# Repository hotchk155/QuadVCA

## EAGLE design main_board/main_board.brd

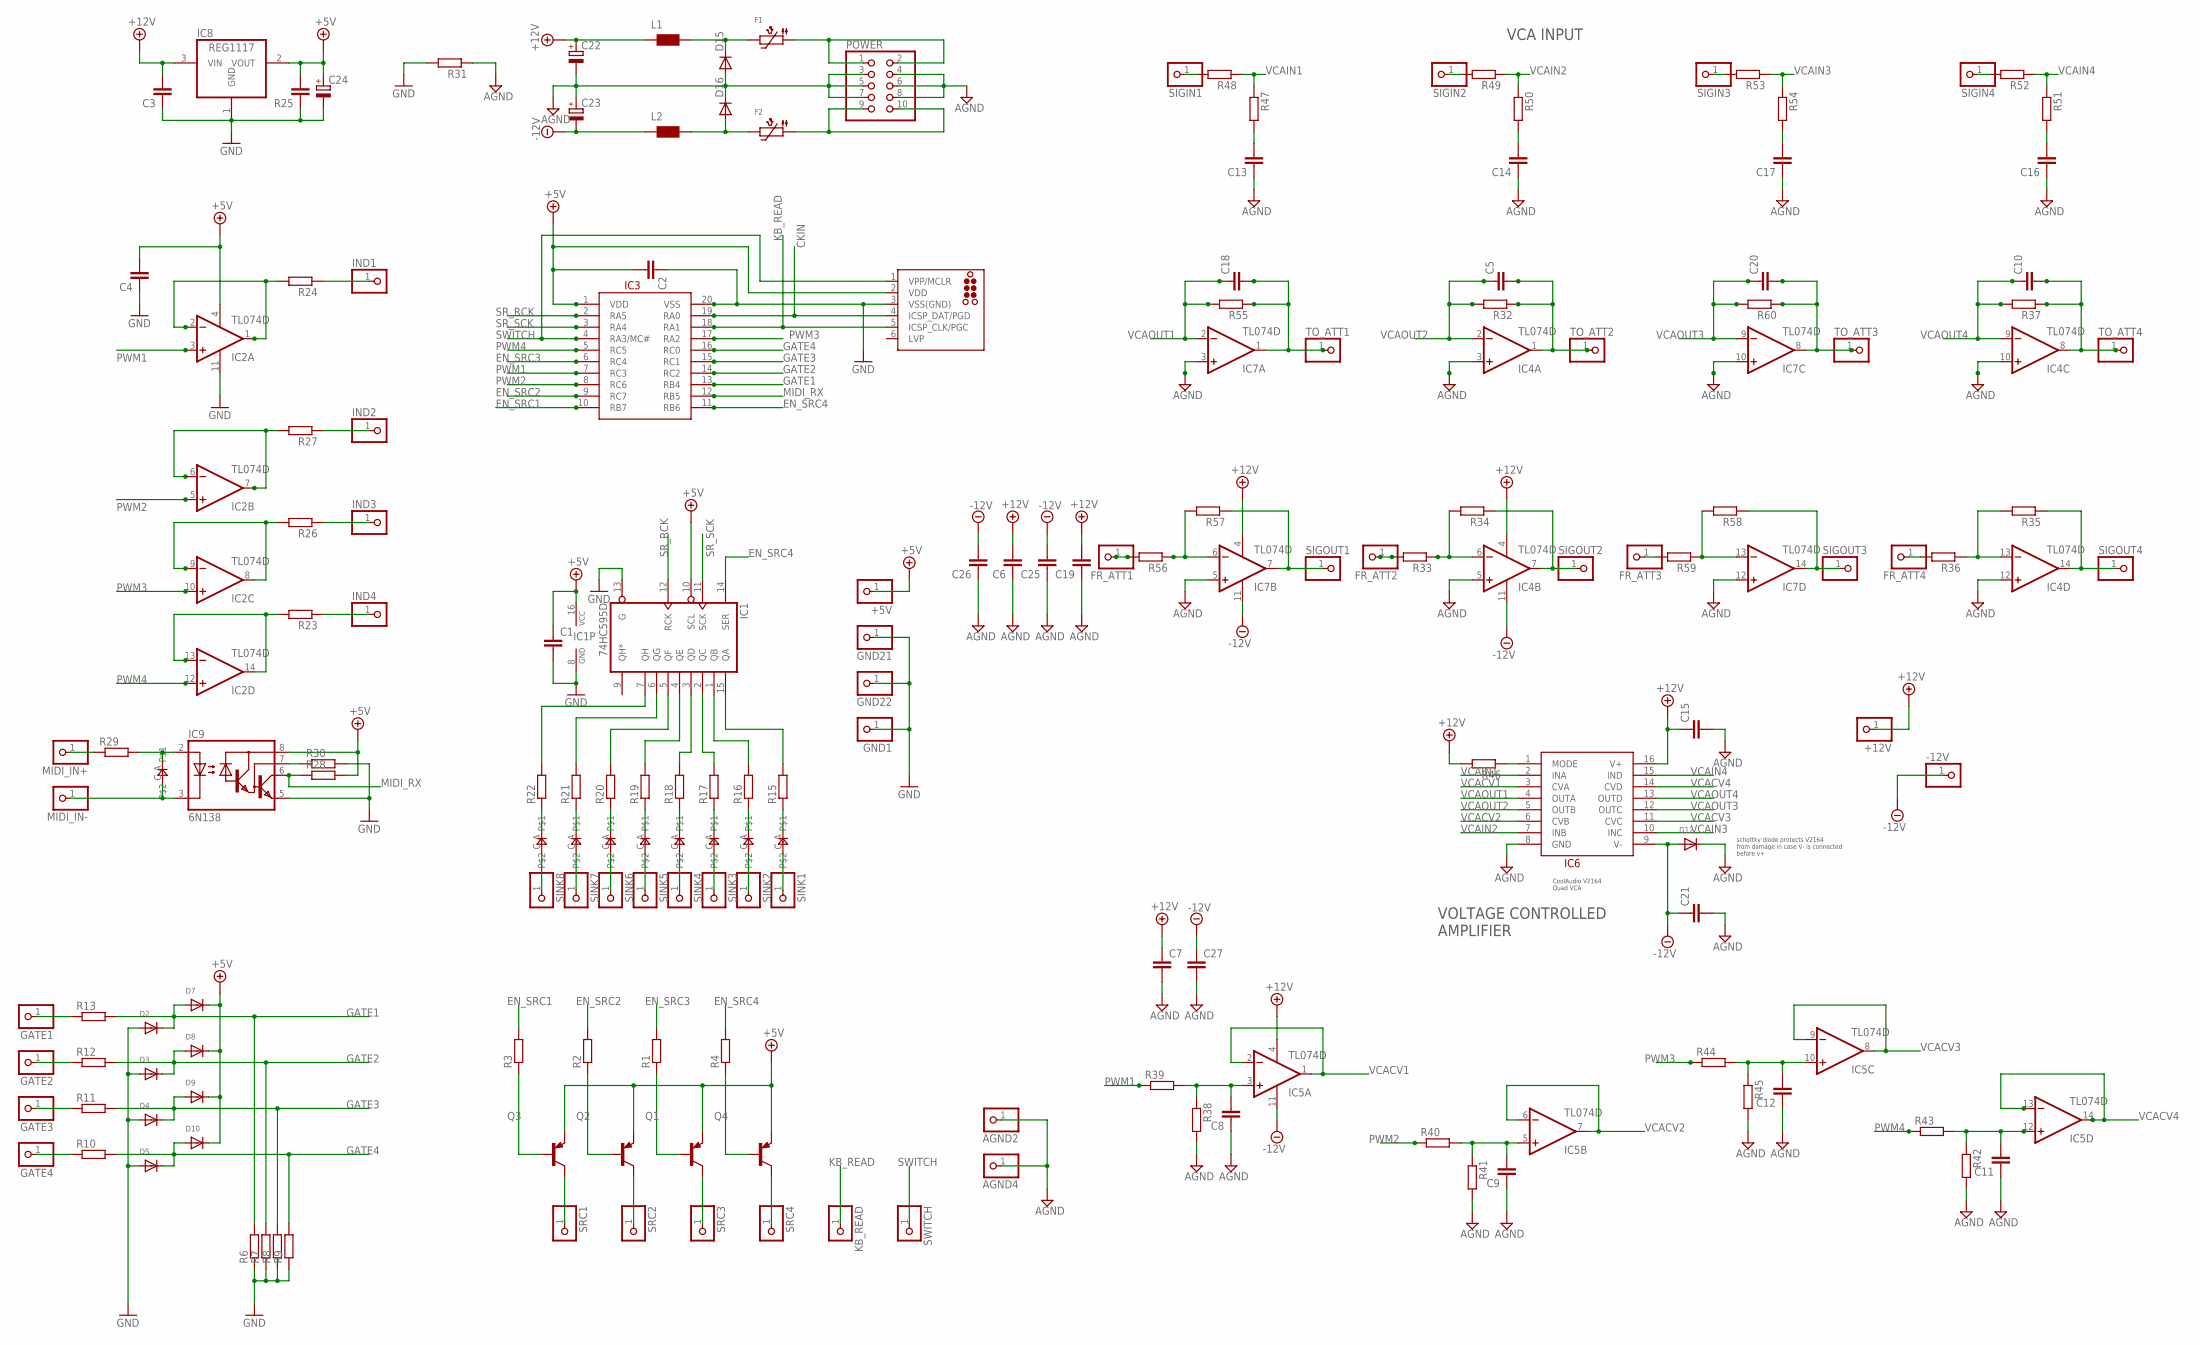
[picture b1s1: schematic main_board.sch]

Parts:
+5V, +12V: PINHD-1X1; 1X01
-12V: PINHD-1X1; 1X01
AGND2, AGND4: PINHD-1X1; 1X01
C1, C2, C3, C4, C5, C6, C7, C8, C9, C10, C11, C12, C13, C14, C15, C16, C17, C18, C19, C20, C21, C25, C26, C27: C-EUC0805; C0805
C22, C23: CPOL-EUE2.5-7; E2,5-7
C24: CPOL-EUE2.5-5; E2,5-5
D2, D3, D4, D5, D7, D8, D9, D10, D12: DIODESOD-123; SOD-123
D11, D13, D14, D17, D18, D19, D20, D21, D22: 0805DIODE
D15, D16: MBR0520LT; SOD123
F1, F2: PTC1210
FR_ATT1, FR_ATT2, FR_ATT3, FR_ATT4: PINHD-1X1; 1X01
GATE1, GATE2, GATE3, GATE4: PINHD-1X1; 1X01
GND1, GND21, GND22: PINHD-1X1; 1X01
IC1: 74HC595D; SO16
IC2, IC4, IC5, IC7: TL074D; SO14
IC3: PIC16F1829SOIC; SO20W
IC6: V2164; SO16
IC8: REG1117; SOT223
IC9: 6N138; DIL08
ICSP: TC2030-MCP-NL
IND1, IND2, IND3, IND4: PINHD-1X1; 1X01
KB_READ: PINHD-1X1; 1X01
L1, L2: WE-CBF_0805; 0805
MIDI_IN+: PINHD-1X1; 1X01
MIDI_IN-: PINHD-1X1; 1X01
POWER: PINHD-2X5; 2X05
Q1, Q2, Q3, Q4: MMBT3906LT1-PNP-SOT23-BEC; SOT23-BEC
R1, R2, R3, R4, R6, R7, R8, R9, R10, R11, R12, R13, R15, R16, R17, R18, R19, R20, R21, R22, R23, R24, R26, R27, R28, R29, R30, R31, R32, R33, R34, R35, R36, R37, R38, R39, R40, R41, R42, R43, R44, R45, R46, R47, R48, R49, R50, R51, R52, R53, R54, R55, R56, R57, R58, R59, R60: R-EU_R0805; R0805
R25: C-EUC0805; C0805
SIGIN1, SIGIN2, SIGIN3, SIGIN4: PINHD-1X1; 1X01
SIGOUT1, SIGOUT2, SIGOUT3, SIGOUT4: PINHD-1X1; 1X01
SINK1, SINK2, SINK3, SINK4, SINK5, SINK6, SINK7, SINK8: PINHD-1X1; 1X01
SRC1, SRC2, SRC3, SRC4: PINHD-1X1; 1X01
SWITCH: PINHD-1X1; 1X01
TO_ATT1, TO_ATT2, TO_ATT3, TO_ATT4: PINHD-1X1; 1X01

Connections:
+5V: +5V.1, C1.1, C2.2, C4.2, C24.+, D7.C, D8.C, D9.C, D10.C, IC1.10 (SCL), IC1.16 (VCC), IC2.4 (V+), IC3.1 (VDD), IC8.2 (VOUT), IC9.8 (VCC), ICSP.2 (VDD), Q1.E, Q2.E, Q3.E, Q4.E, R25.2, R28.2
+12V: +12V.1, C3.2, C6.2, C7.1, C15.1, C19.2, C22.+, IC4.4 (V+), IC5.4 (V+), IC6.16 (V+), IC7.4 (V+), IC8.3 (VIN), L1.1, R46.2
-12V: -12V.1, C21.1, C23.-, C25.2, C26.2, C27.1, D12.A, IC4.11 (V-), IC5.11 (V-), IC6.9 (V-), IC7.11 (V-), L2.1
AGND: AGND2.1, AGND4.1, C6.1, C7.2, C8.1, C9.1, C11.1, C12.1, C13.1, C14.1, C15.2, C16.1, C17.1, C19.1, C21.2, C22.-, C23.+, C25.1, C26.1, C27.2, D12.C, D15.A, D16.C, IC4.3 (+IN), IC4.5 (+IN), IC4.10 (+IN), IC4.12 (+IN), IC6.8 (GND), IC7.3 (+IN), IC7.5 (+IN), IC7.10 (+IN), IC7.12 (+IN), POWER.3, POWER.4, POWER.5, POWER.6, POWER.7, POWER.8, R31.1, R38.2, R41.2, R42.2, R45.2
CKIN: IC3.19 (RA0), ICSP.4 (ICSP_DAT/PGD)
EN_SRC1: IC3.10 (RB7), R3.2
EN_SRC2: IC3.9 (RC7), R2.2
EN_SRC3: IC3.6 (RC4), R1.2
EN_SRC4: IC1.14 (SER), IC3.11 (RB6), R4.2
FR_ATT1: FR_ATT1.1, R56.2
GATE1: D2.C, D7.A, IC3.13 (RB4), R6.2, R13.2
GATE2: D3.C, D8.A, IC3.14 (RC2), R7.2, R12.2
GATE3: D4.C, D9.A, IC3.15 (RC1), R8.2, R11.2
GATE4: D5.C, D10.A, IC3.16 (RC0), R9.2, R10.2
GND: C1.2, C2.1, C3.1, C4.1, C24.-, D2.A, D3.A, D4.A, D5.A, GND1.1, GND21.1, GND22.1, IC1.8 (GND), IC1.13 (G), IC2.11 (V-), IC3.20 (VSS), IC8.1 (GND), IC9.5 (GND), ICSP.3 (VSS(GND)), R6.1, R7.1, R8.1, R9.1, R25.1, R30.2, R31.2
KB_READ: IC3.18 (RA1), ICSP.5 (ICSP_CLK/PGC), KB_READ.1
MIDI_RX: IC3.12 (RB5), IC9.6 (VO), R28.1
unnamed: IC1.7 (QH), R22.2
unnamed: IC1.6 (QG), R21.2
unnamed: IC1.5 (QF), R20.2
unnamed: IC1.4 (QE), R19.2
unnamed: IC1.3 (QD), R18.2
unnamed: IC1.2 (QC), R17.2
unnamed: IC1.1 (QB), R16.2
unnamed: IC1.15 (QA), R15.2
unnamed: D13.A, R22.1
unnamed: D14.A, R21.1
unnamed: D17.A, R20.1
unnamed: D18.A, R19.1
unnamed: D19.A, R18.1
unnamed: D20.A, R17.1
unnamed: D21.A, R16.1
unnamed: D22.A, R15.1
unnamed: Q3.C, SRC1.1
unnamed: Q2.C, SRC2.1
unnamed: Q1.C, SRC3.1
unnamed: Q4.C, SRC4.1
unnamed: IC6.1 (MODE), R46.1
unnamed: Q3.B, R3.1
unnamed: Q2.B, R2.1
unnamed: Q1.B, R1.1
unnamed: Q4.B, R4.1
unnamed: D13.C, SINK8.1
unnamed: IC7.6 (-IN), R56.1, R57.2
unnamed: IC7.7 (OUT), R57.1, SIGOUT1.1
unnamed: D14.C, SINK7.1
unnamed: IC7.13 (-IN), R58.2, R59.1
unnamed: IC7.14 (OUT), R58.1, SIGOUT3.1
unnamed: D15.C, F1.P$2 (2), L1.2
unnamed: IC4.6 (-IN), R33.1, R34.2
unnamed: IC4.7 (OUT), R34.1, SIGOUT2.1
unnamed: D16.A, F2.P$2 (2), L2.2
unnamed: IC4.13 (-IN), R35.2, R36.1
unnamed: IC4.14 (OUT), R35.1, SIGOUT4.1
unnamed: C13.2, R47.2
unnamed: R48.2, SIGIN1.1
unnamed: C14.2, R50.2
unnamed: R49.2, SIGIN2.1
unnamed: C17.2, R54.2
unnamed: R53.2, SIGIN3.1
unnamed: C16.2, R51.2
unnamed: R52.2, SIGIN4.1
unnamed: IND1.1, R24.1
unnamed: IC2.1 (OUT), IC2.2 (-IN), R24.2
unnamed: C8.2, IC5.3 (+IN), R38.1, R39.2
unnamed: D17.C, SINK6.1
unnamed: IC2.6 (-IN), IC2.7 (OUT), R27.2
unnamed: IND2.1, R27.1
unnamed: C9.2, IC5.5 (+IN), R40.2, R41.1
unnamed: IC2.8 (OUT), IC2.9 (-IN), R26.2
unnamed: IND3.1, R26.1
unnamed: C12.2, IC5.10 (+IN), R44.2, R45.1
unnamed: IC2.13 (-IN), IC2.14 (OUT), R23.2
unnamed: IND4.1, R23.1
unnamed: C11.2, IC5.12 (+IN), R42.1, R43.2
unnamed: D18.C, SINK5.1
unnamed: FR_ATT2.1, R33.2
unnamed: GATE1.1, R13.1
unnamed: IC9.7 (VB), R30.1
unnamed: F2.P$1 (1), POWER.9, POWER.10
unnamed: D11.A, IC9.2 (A), R29.2
unnamed: D11.C, IC9.3 (C), MIDI_IN-.1
unnamed: MIDI_IN+.1, R29.1
unnamed: GATE2.1, R12.1
unnamed: GATE3.1, R11.1
unnamed: GATE4.1, R10.1
unnamed: FR_ATT3.1, R59.2
unnamed: FR_ATT4.1, R36.2
unnamed: D19.C, SINK4.1
unnamed: D20.C, SINK3.1
unnamed: F1.P$1 (1), POWER.1, POWER.2
unnamed: D21.C, SINK2.1
unnamed: D22.C, SINK1.1
PWM1: IC2.3 (+IN), IC3.7 (RC3), R39.1
PWM2: IC2.5 (+IN), IC3.8 (RC6), R40.1
PWM3: IC2.10 (+IN), IC3.17 (RA2), R44.1
PWM4: IC2.12 (+IN), IC3.5 (RC5), R43.1
SR_RCK: IC1.12 (RCK), IC3.2 (RA5)
SR_SCK: IC1.11 (SCK), IC3.3 (RA4)
SWITCH: IC3.4 (RA3/MC#), ICSP.1 (VPP/MCLR), SWITCH.1
TO_ATT1: C18.2, IC7.1 (OUT), R55.1, TO_ATT1.1
TO_ATT2: C5.2, IC4.1 (OUT), R32.1, TO_ATT2.1
TO_ATT3: C20.2, IC7.8 (OUT), R60.1, TO_ATT3.1
TO_ATT4: C10.2, IC4.8 (OUT), R37.1, TO_ATT4.1
VCACV1: IC5.1 (OUT), IC5.2 (-IN), IC6.3 (CVA)
VCACV2: IC5.6 (-IN), IC5.7 (OUT), IC6.6 (CVB)
VCACV3: IC5.8 (OUT), IC5.9 (-IN), IC6.11 (CVC)
VCACV4: IC5.13 (-IN), IC5.14 (OUT), IC6.14 (CVD)
VCAIN1: IC6.2 (INA), R47.1, R48.1
VCAIN2: IC6.7 (INB), R49.1, R50.1
VCAIN3: IC6.10 (INC), R53.1, R54.1
VCAIN4: IC6.15 (IND), R51.1, R52.1
VCAOUT1: C18.1, IC6.4 (OUTA), IC7.2 (-IN), R55.2
VCAOUT2: C5.1, IC4.2 (-IN), IC6.5 (OUTB), R32.2
VCAOUT3: C20.1, IC6.12 (OUTC), IC7.9 (-IN), R60.2
VCAOUT4: C10.1, IC4.9 (-IN), IC6.13 (OUTD), R37.2

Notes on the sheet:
schottky diode protects V2164 from damage in case V- is connected before v+
CoolAudio V2164 Quad VCA
VCA INPUT
VOLTAGE CONTROLLED AMPLIFIER

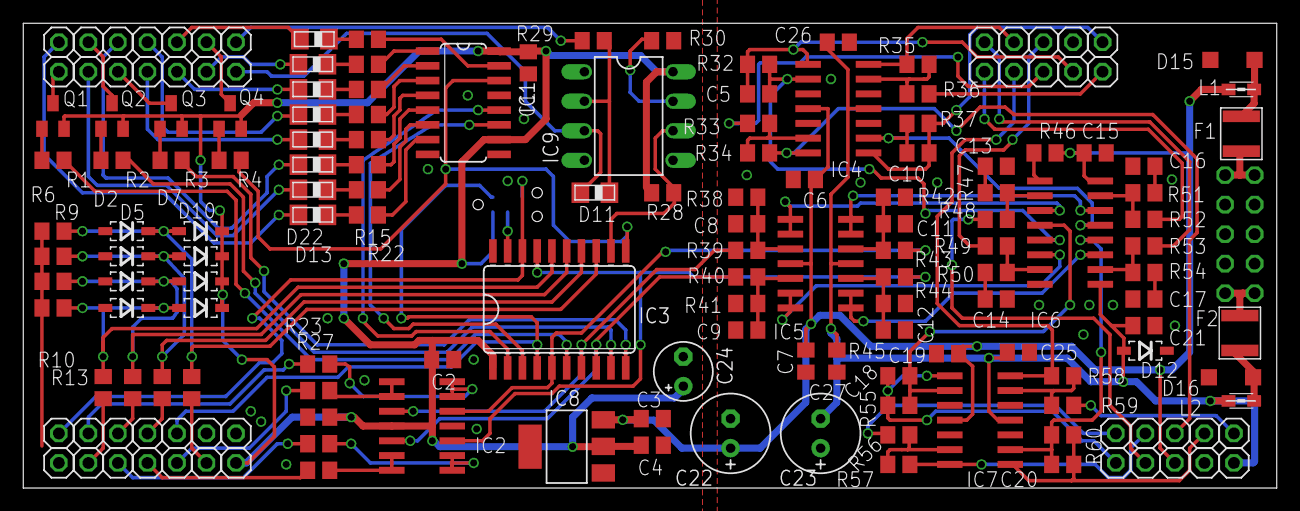
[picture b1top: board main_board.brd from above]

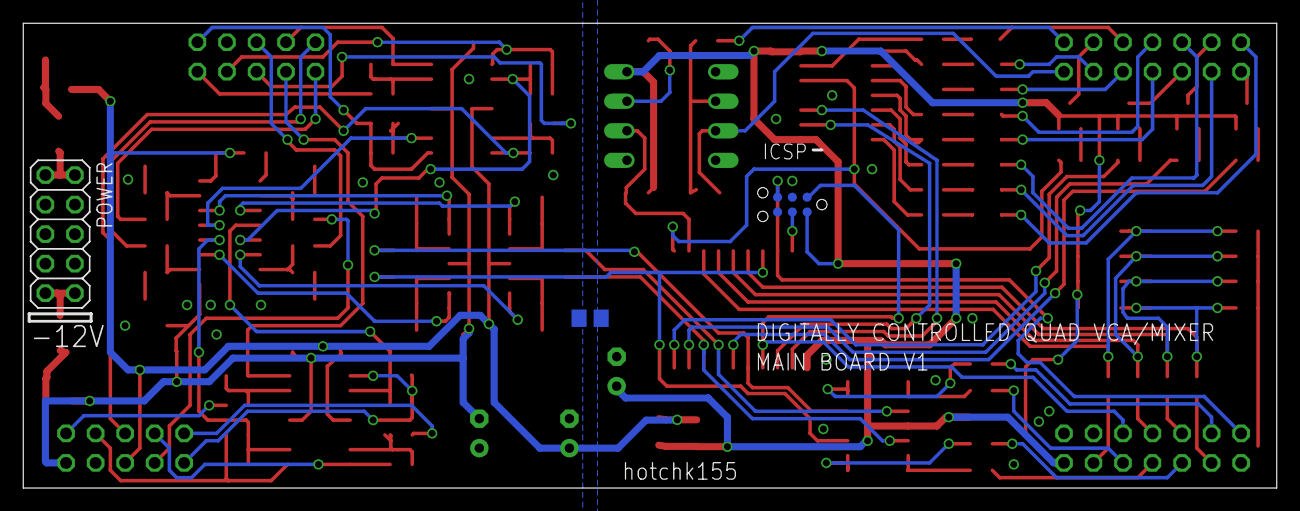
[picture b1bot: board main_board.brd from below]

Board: 2 copper layers, 107.8 x 40.0 mm, 172 parts (3 on the bottom side), 116 nets.

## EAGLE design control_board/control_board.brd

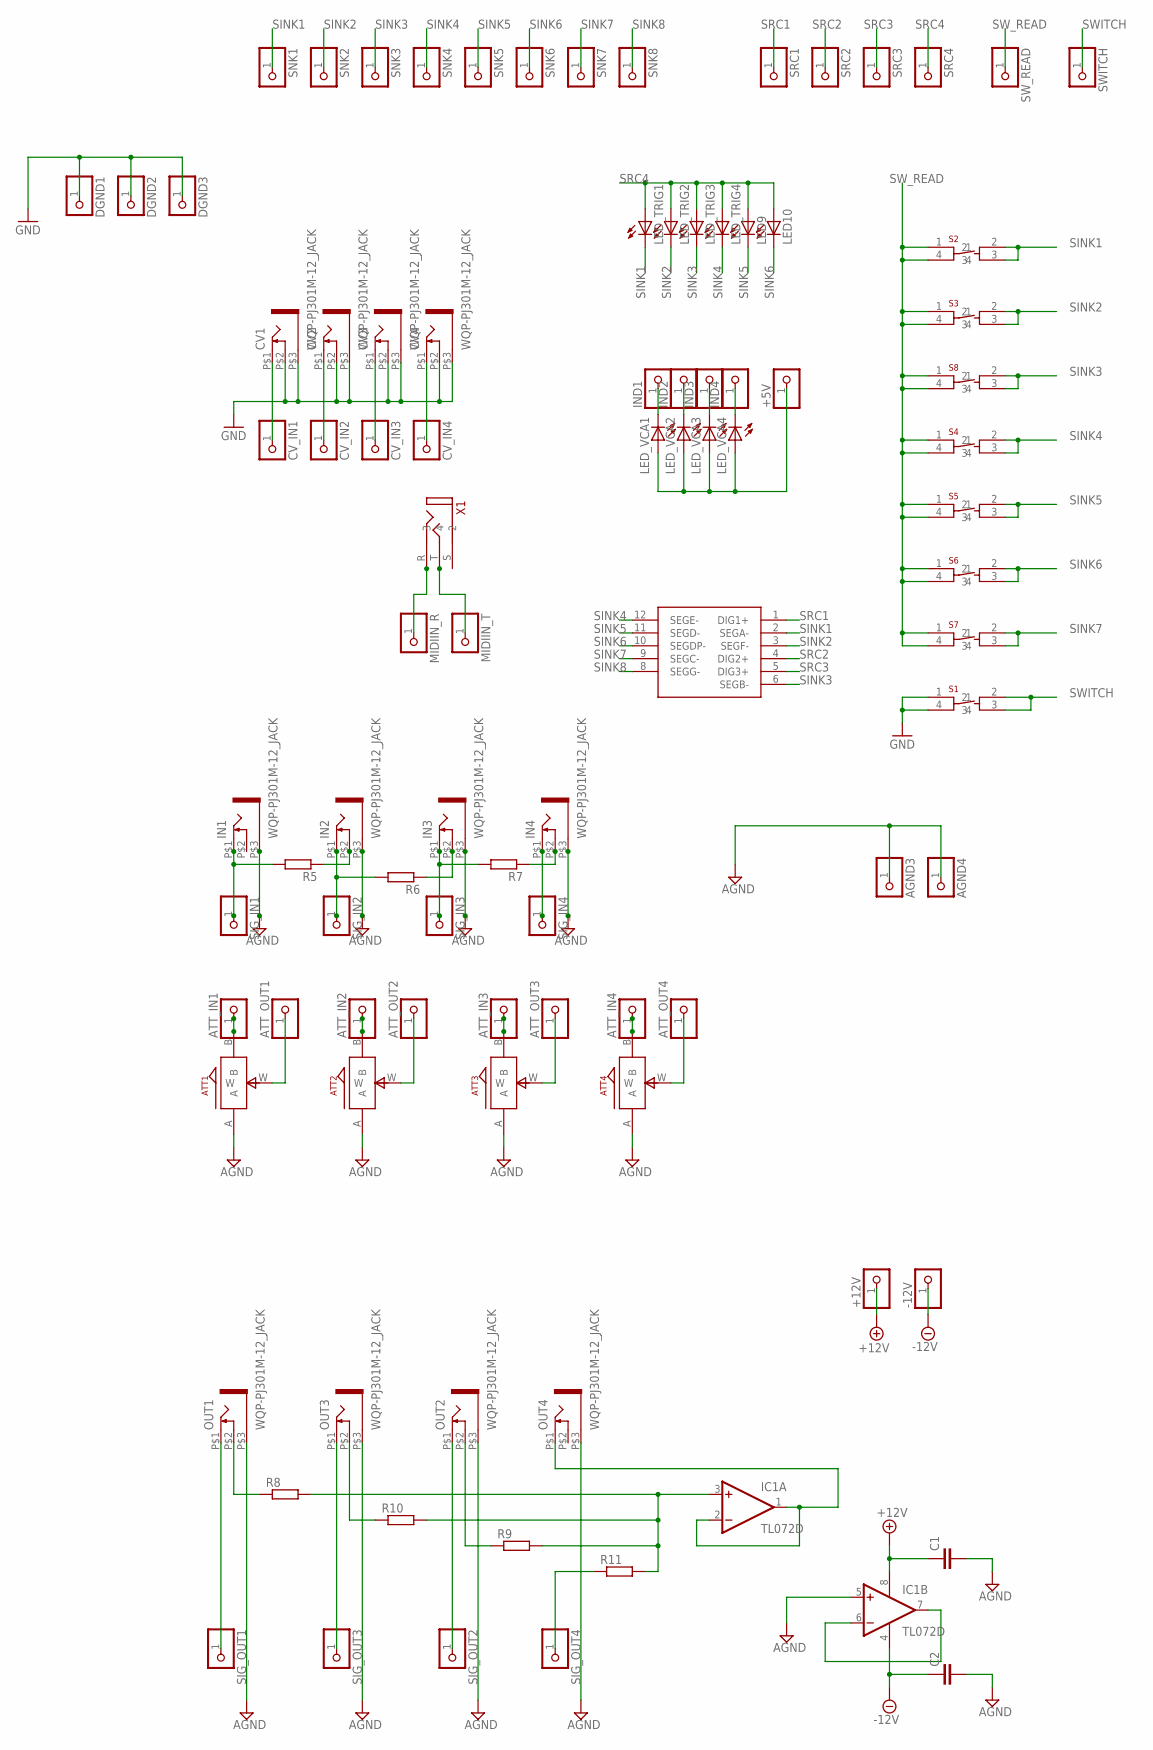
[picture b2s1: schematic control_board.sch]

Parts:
+5V, +12V: PINHD-1X1; 1X01
-12V: PINHD-1X1; 1X01
AGND3, AGND4: PINHD-1X1; 1X01
ATT1, ATT2, ATT3, ATT4: ALPS_POT_SMALL; SMALL_ALPS_POT
ATT_IN1, ATT_IN2, ATT_IN3, ATT_IN4: PINHD-1X1; 1X01
ATT_OUT1, ATT_OUT2, ATT_OUT3, ATT_OUT4: PINHD-1X1; 1X01
C1, C2: C-EUC0805; C0805
CV1, CV2, CV3, CV4: WQP-PJ301M-12_JACK
CV_IN1, CV_IN2, CV_IN3, CV_IN4: PINHD-1X1; 1X01
DGND1, DGND2, DGND3: PINHD-1X1; 1X01
DISP1: KYX2381_TRIPLE7SEG
IC1: TL072D; SO08
IN1, IN2, IN3, IN4: WQP-PJ301M-12_JACK
IND1, IND2, IND3, IND4: PINHD-1X1; 1X01
LED9, LED10: LED3MM
LED_TRIG1, LED_TRIG2, LED_TRIG3, LED_TRIG4: LED3MM
LED_VCA1, LED_VCA2, LED_VCA3, LED_VCA4: LED3MM
MIDIIN_R: PINHD-1X1; 1X01
MIDIIN_T: PINHD-1X1; 1X01
OUT1, OUT2, OUT3, OUT4: WQP-PJ301M-12_JACK
R5, R6, R7, R8, R9, R10, R11: R-EU_R0805; R0805
S1, S2, S3, S4, S5, S6, S7, S8: 6MM_TACT; 6MMTACT
SIG_IN1, SIG_IN2, SIG_IN3, SIG_IN4: PINHD-1X1; 1X01
SIG_OUT1, SIG_OUT2, SIG_OUT3, SIG_OUT4: PINHD-1X1; 1X01
SNK1, SNK2, SNK3, SNK4, SNK5, SNK6, SNK7, SNK8: PINHD-1X1; 1X01
SRC1, SRC2, SRC3, SRC4: PINHD-1X1; 1X01
SWITCH: PINHD-1X1; 1X01
SW_READ: PINHD-1X1; 1X01
X1: VERTICAL_3_5MM_SOCKETTHONK; PJ301CM

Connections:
+5V: +5V.1, LED_VCA1.A, LED_VCA2.A, LED_VCA3.A, LED_VCA4.A
+12V: +12V.1, C1.1, IC1.8 (V+)
-12V: -12V.1, C2.1, IC1.4 (V-)
AGND: AGND3.1, AGND4.1, ATT1.A, ATT2.A, ATT3.A, ATT4.A, C1.2, C2.2, IC1.5 (+IN), IN1.P$3 (1), IN2.P$3 (1), IN3.P$3 (1), IN4.P$3 (1), OUT1.P$3 (1), OUT2.P$3 (1), OUT3.P$3 (1), OUT4.P$3 (1)
GND: CV1.P$2 (3), CV1.P$3 (1), CV2.P$2 (3), CV2.P$3 (1), CV3.P$2 (3), CV3.P$3 (1), CV4.P$2 (3), CV4.P$3 (1), DGND1.1, DGND2.1, DGND3.1, S1.1, S1.4
unnamed: ATT1.W, ATT_OUT1.1
unnamed: ATT1.B, ATT_IN1.1
unnamed: ATT3.W, ATT_OUT3.1
unnamed: ATT2.B, ATT_IN2.1
unnamed: ATT2.W, ATT_OUT2.1
unnamed: ATT3.B, ATT_IN3.1
unnamed: ATT4.W, ATT_OUT4.1
unnamed: ATT4.B, ATT_IN4.1
unnamed: OUT1.P$2 (3), R8.1
unnamed: IN2.P$1 (2), R6.2, SIG_IN2.1
unnamed: IN3.P$1 (2), R7.2, SIG_IN3.1
unnamed: IN4.P$1 (2), SIG_IN4.1
unnamed: CV1.P$1 (2), CV_IN1.1
unnamed: CV2.P$1 (2), CV_IN2.1
unnamed: CV3.P$1 (2), CV_IN3.1
unnamed: CV4.P$1 (2), CV_IN4.1
unnamed: OUT1.P$1 (2), SIG_OUT1.1
unnamed: MIDIIN_R.1, X1.R (3)
unnamed: MIDIIN_T.1, X1.T (4)
unnamed: IND1.1, LED_VCA1.K (C)
unnamed: IND2.1, LED_VCA2.K (C)
unnamed: IND3.1, LED_VCA3.K (C)
unnamed: IND4.1, LED_VCA4.K (C)
unnamed: OUT3.P$1 (2), SIG_OUT3.1
unnamed: OUT2.P$1 (2), SIG_OUT2.1
unnamed: R11.1, SIG_OUT4.1
unnamed: IN2.P$2 (3), R5.1
unnamed: IN3.P$2 (3), R6.1
unnamed: IN4.P$2 (3), R7.1
unnamed: IN1.P$1 (2), R5.2, SIG_IN1.1
unnamed: OUT3.P$2 (3), R10.1
unnamed: OUT2.P$2 (3), R9.1
unnamed: IC1.3 (+IN), R8.2, R9.2, R10.2, R11.2
unnamed: IC1.1 (OUT), IC1.2 (-IN), OUT4.P$1 (2)
unnamed: IC1.6 (-IN), IC1.7 (OUT)
SINK1: DISP1.2 (SEGA-), LED_TRIG1.K (C), S2.2, S2.3, SNK1.1
SINK2: DISP1.3 (SEGF-), LED_TRIG2.K (C), S3.2, S3.3, SNK2.1
SINK3: DISP1.6 (SEGB-), LED_TRIG3.K (C), S8.2, S8.3, SNK3.1
SINK4: DISP1.12 (SEGE-), LED_TRIG4.K (C), S4.2, S4.3, SNK4.1
SINK5: DISP1.11 (SEGD-), LED9.K (C), S5.2, S5.3, SNK5.1
SINK6: DISP1.10 (SEGDP-), LED10.K (C), S6.2, S6.3, SNK6.1
SINK7: DISP1.9 (SEGC-), S7.2, S7.3, SNK7.1
SINK8: DISP1.8 (SEGG-), SNK8.1
SRC1: DISP1.1 (DIG1+), SRC1.1
SRC2: DISP1.4 (DIG2+), SRC2.1
SRC3: DISP1.5 (DIG3+), SRC3.1
SRC4: LED9.A, LED10.A, LED_TRIG1.A, LED_TRIG2.A, LED_TRIG3.A, LED_TRIG4.A, SRC4.1
SWITCH: S1.2, S1.3, SWITCH.1
SW_READ: S2.1, S2.4, S3.1, S3.4, S4.1, S4.4, S5.1, S5.4, S6.1, S6.4, S7.1, S7.4, S8.1, S8.4, SW_READ.1

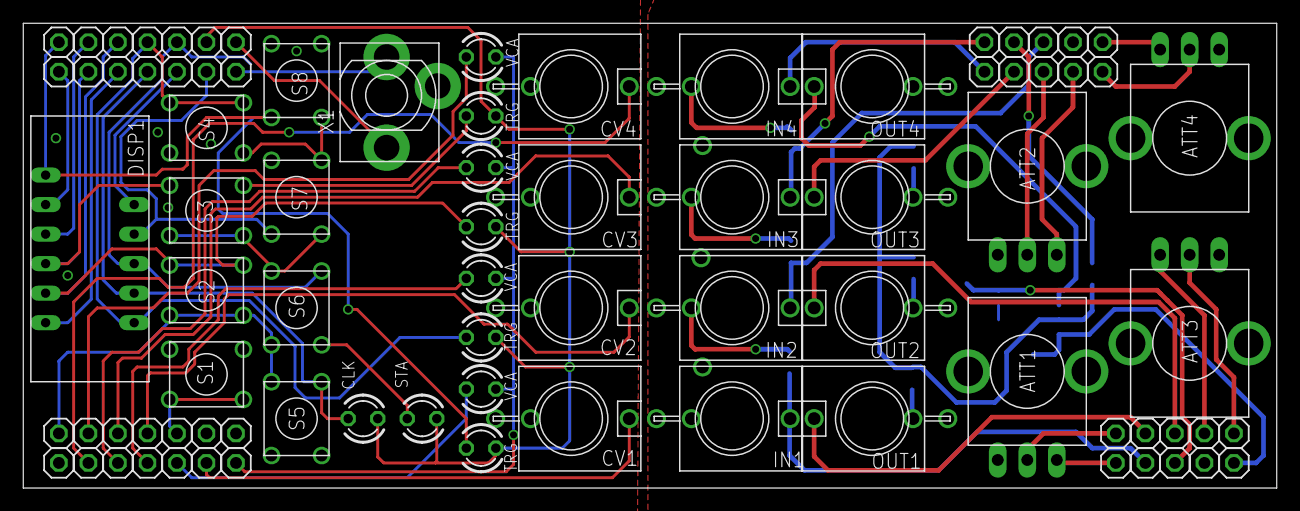
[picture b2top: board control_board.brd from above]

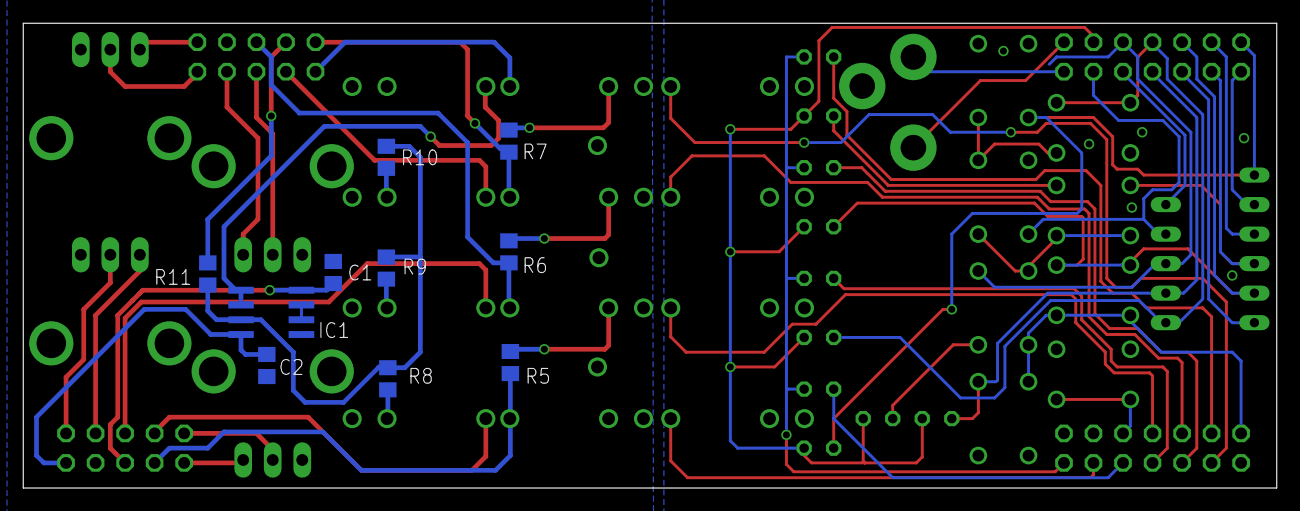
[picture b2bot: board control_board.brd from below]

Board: 2 copper layers, 107.8 x 40.0 mm, 94 parts (10 on the bottom side), 54 nets.

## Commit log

2017-07-07 :tada: Added .gitattributes & .gitignore files
2017-07-09 in work
2017-07-10 moar stuffs
2017-07-10 and more
2017-07-10 MORE
2017-08-02 coding jazz
2017-08-13 code etc
2017-08-17 stuff
2017-08-20 sdsad
2017-08-26 adda
2017-09-05 dweew
2017-09-06 fixes

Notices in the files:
parts and their libraries:
tag-connect: ©2009 ROFA.cz - modified and updated by Robert Darlington ‹rdarlington@gmail.com›
wuerth-elektronik: Copyright: Würth Elektronik eiSos
